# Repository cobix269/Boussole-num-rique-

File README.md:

# NORHALO

NORHALO est un projet de boussole numérique réalisé à l’aide d’un PCB qui permet à son utilisateur de retrouver le nord magnétique même dans le noir. Un écran lumineux affiche une flèche qui indique le nord grâce à un magnétomètre, des LEDs s’allument en fonction de la direction dans laquelle pointe la flèche.

**Figure 1 & 2 : visualisation 3D du PCB **  :    

## À propos :

Le projet est réalisé sous KiCad et comprend actuellement la conception du schéma électronique ainsi que celle du circuit imprimé et le code a implémenté dans le microcontrôleur.

## Composantes principales

| Type de composant | Référence / Modèle |
| :--- | :--- |
| **Accéléromètre** | MPU-6050 |
| **Alimentation** | USB-C |
| **Ecran** | *Non spécifié* |
| **LEDs** | WS2812B |
| **Level shifter** | 74AHCT1G125 |
| **Magnétomètre** | MMC5883MA |
| **Microcontrôleur** | STM32G071KBTxN |
| **Régulateur 3,3V** | AP2112K-3.3 |

---

**Fonctionnement** :

Le MMC5883MA est utilisé comme capteur magnétique pour mesurer le champ magnétique terrestre.

Le MPU-6050 apporte les informations inertielles permettant de prendre en compte l'orientation et les mouvements de la carte par rapport au sol.

Les données des capteurs sont traitées par le STM32G071KBTxN, qui peut déterminer la représentation de la direction à afficher.

Le code permet de fusionner ces données pour calculer un cap précis (compensé en inclinaison), puis met à jour l'écran central et pilote les LEDs (WS2812B) afin d'indiquer l'orientation.

## Alimentation :

La carte est prévue pour être alimentée via USB-C.

L'alimentation est ensuite régulée par un AP2112K-3.3 afin de fournir le domaine d'alimentation aux circuits fonctionnant en 3,3 V comme le microcontrôleur.

Le 74AHCT1G125 est utilisé dans la chaîne de commande des LED afin d'assurer l'interface logique entre le microcontrôleur et les WS2812B.

Les résistances sont utilisées comme résistance de pull-up pour le bus I2C, pour la configuration USB-C et pour la chaîne de commande des LEDs

Les condensateurs sont utilisés pour assurer le découplage local des circuits intégrés, la stabilisation de l’alimentation et le filtrage des variations rapides de tension.

Pour le placement des composants il est important que les condensateurs de découplage soient placés au plus près des composants qu’ils doivent découpler afin de réduire la longueur des connexions.

## Structure du projet

```text
.
└── Code_boussole 	       # code du projet               
    ├── Projet1.kicad_sch      # Schéma principal
    ├── Projet1.kicad_pcb      # Circuit imprimé
    ├── LED20.kicad_sch        # Schéma de l'affichage LED
    └── README.md              # Documentation du projet
```
Améliorations futures :

Passer sur batterie (LiPo / Li-Ion) : Ajoute un régulateur de charge USB et un circuit de basculement automatique entre l'USB et la batterie

Mesure de tension batterie : Ajoute un pont diviseur de tension connecté à une entrée ADC du STM32 pour afficher le pourcentage de batterie restant sur l'écran rond

Fusible réarmable : Ajoute une protection contre les surintensités juste après VBUS.

Visualisation du projet généré par IA :

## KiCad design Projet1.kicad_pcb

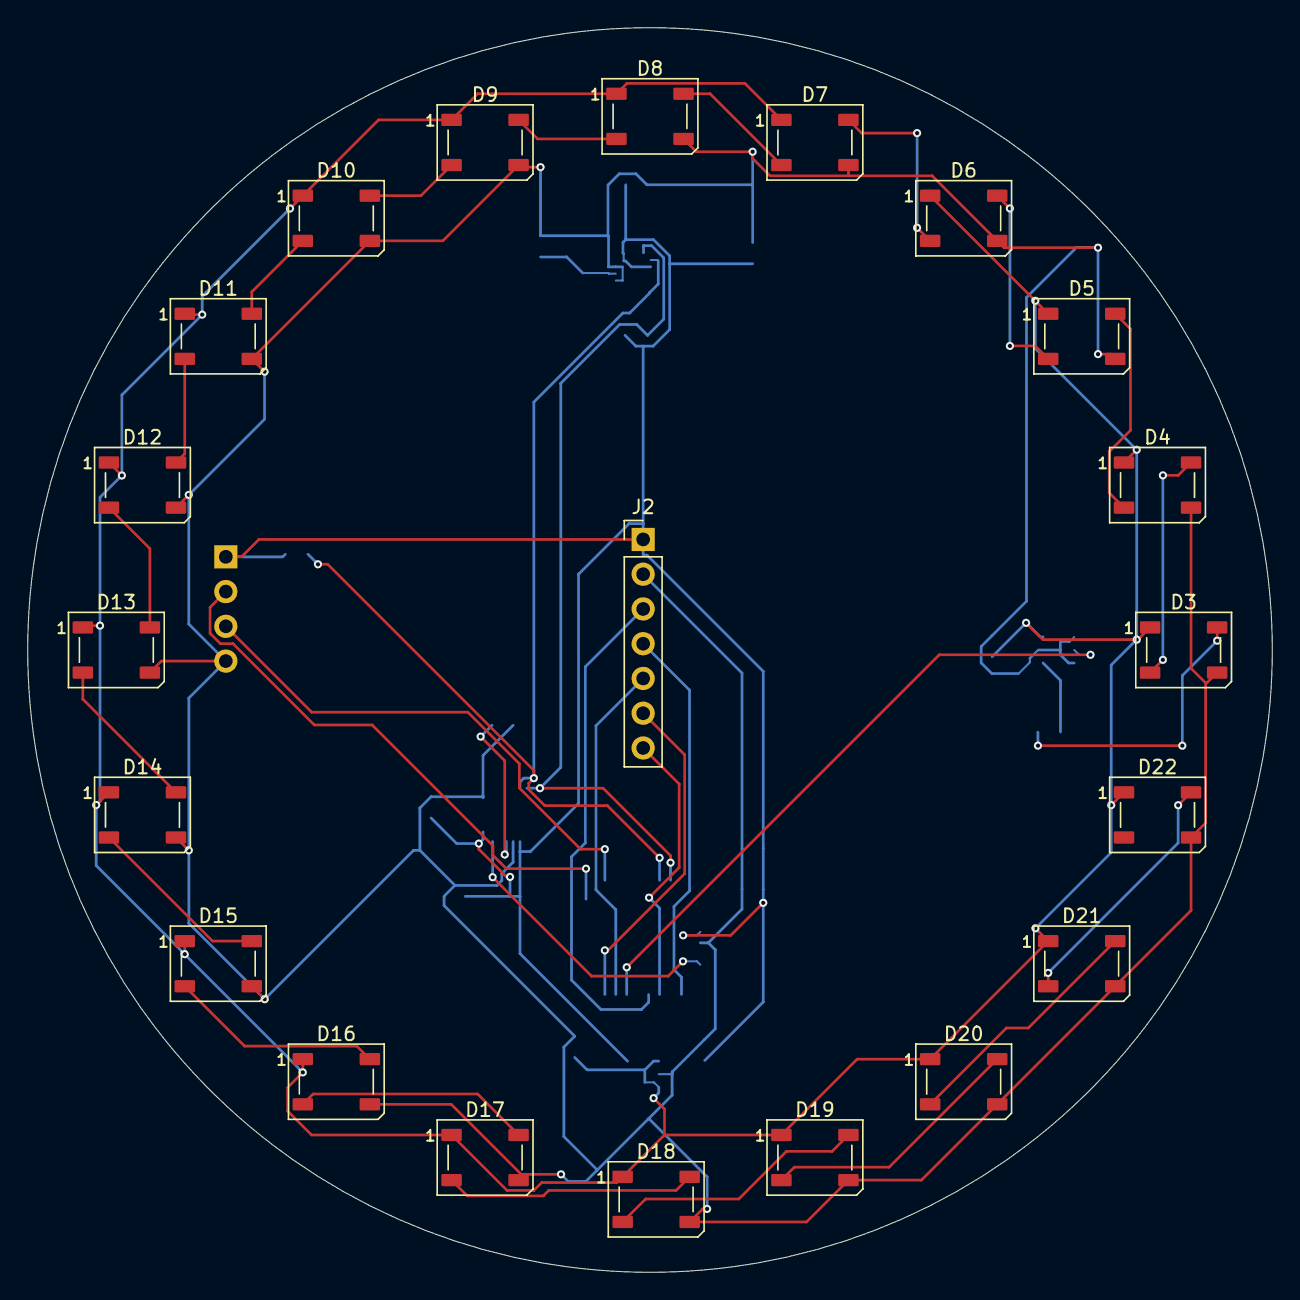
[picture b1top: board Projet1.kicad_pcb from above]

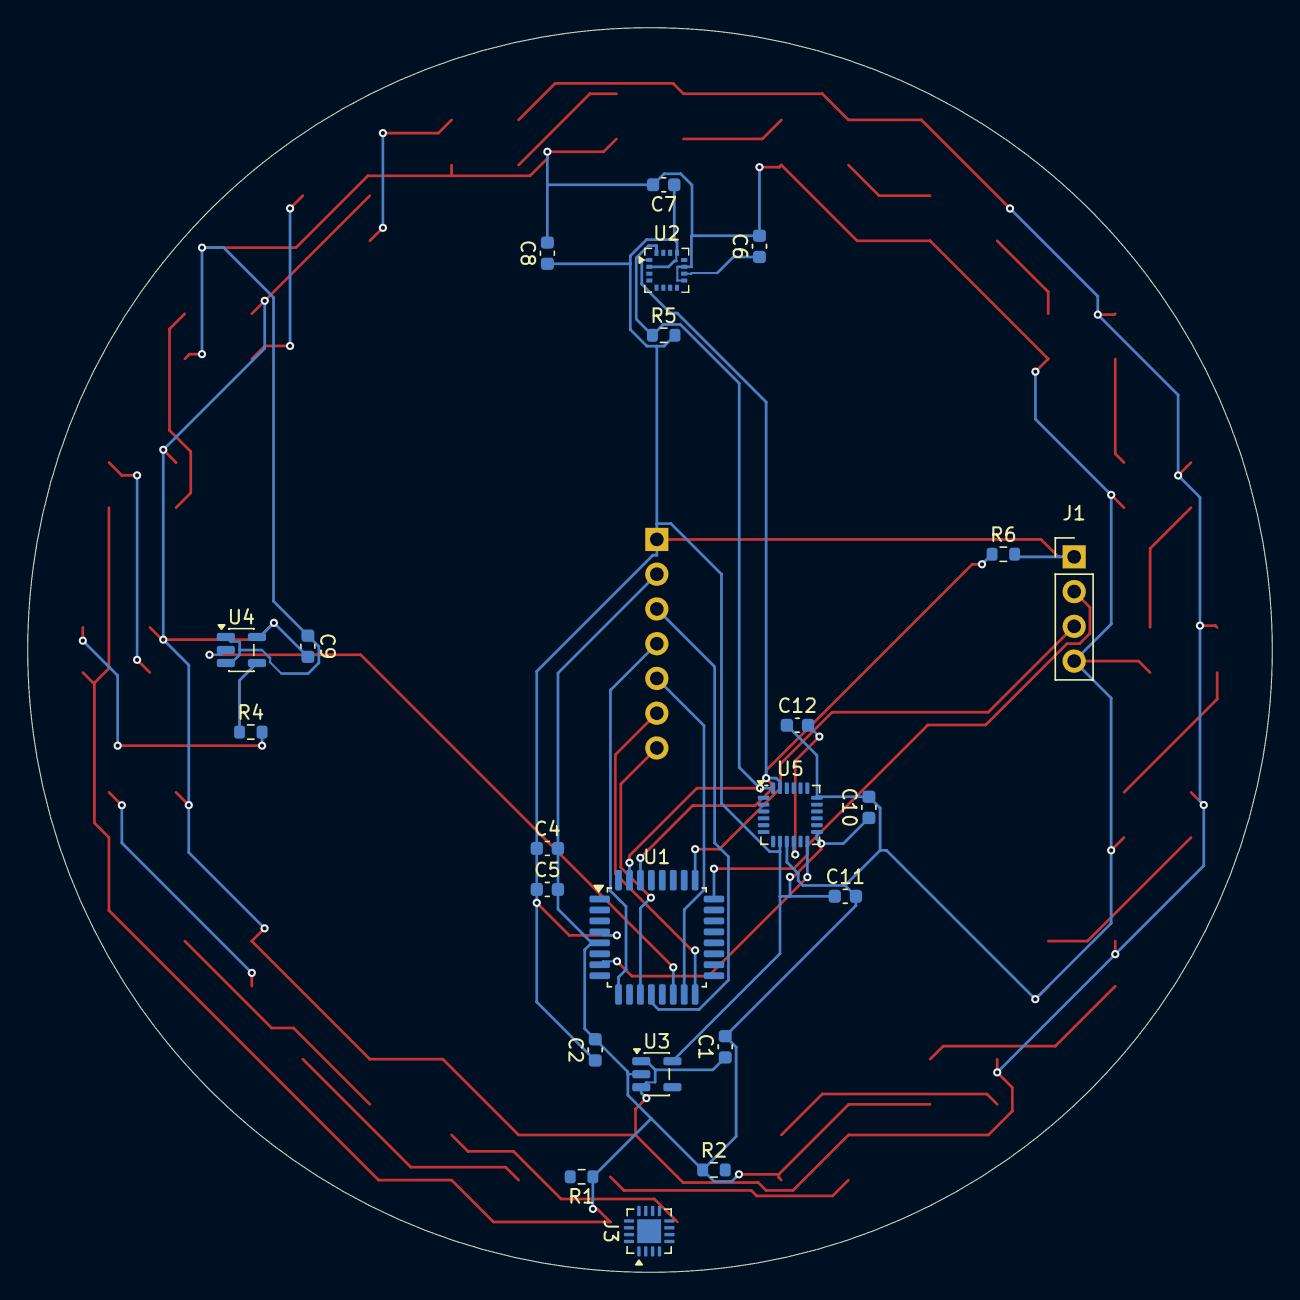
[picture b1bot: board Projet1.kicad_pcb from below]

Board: 2 copper layers, 91.0 x 91.0 mm, 44 parts (23 on the bottom side), 37 nets.

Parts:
C1, C2, C7: 1 µF; C_0603_1608Metric
C4, C8, C10: 100 nF; C_0603_1608Metric
C5: 4.7 µF; C_0603_1608Metric
C6: 10 µF; C_0603_1608Metric
C9: 100nF; C_0603_1608Metric
C11: 10; C_0603_1608Metric
C12: 10 nF; C_0603_1608Metric
D3, D4, D5, D6, D7, D8, D9, D10, D11, D12, D13, D14, D15, D16, D17, D18, D19, D20, D21, D22: WS2812B; LED_WS2812B_PLCC4_5.0x5.0mm_P3.2mm
J1: Conn_01x04; PinHeader_1x04_P2.54mm_Vertical
J2: Conn_01x07; PinHeader_1x07_P2.54mm_Vertical
J3: USB_C_Receptacle_PowerOnly_6P; WQFN-16-1EP_3x3mm_P0.5mm_EP1.75x1.75mm
R1, R2: 5.1 k; R_0603_1608Metric
R4: 330; R_0603_1608Metric
R5, R6: 2.7k; R_0603_1608Metric
U1: STM32G071KBTxN; LQFP-32_7x7mm_P0.8mm
U2: MMC5883MA; LGA-16_3x3mm_P0.5mm
U3: AP2112K-3.3; SOT-23-5
U4: 74AHCT1G125; SOT-23-5
U5: MPU-6050; InvenSense_QFN-24_4x4mm_P0.5mm

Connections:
+3.3V: C2.1, C4.1, C5.1, C7.1, C8.1, C10.1, C11.1, J1.1, J2.1, R5.2, R6.2, U1.4 (VDD), U2.2 (VDD), U2.13 (VDDIO), U3.5 (VOUT), U5.8 (VLOGIC), U5.13 (VDD)
+5V: C1.1, C9.2, D3.1 (VDD), D4.1 (VDD), D5.1 (VDD), D6.1 (VDD), D7.1 (VDD), D8.1 (VDD), D9.1 (VDD), D10.1 (VDD), D11.1 (VDD), D12.1 (VDD), D13.1 (VDD), D14.1 (VDD), D15.1 (VDD), D16.1 (VDD), D17.1 (VDD), D18.1 (VDD), D19.1 (VDD), D20.1 (VDD), D21.1 (VDD), D22.1 (VDD), U3.1 (VIN), U3.3 (EN), U4.5 (VCC)
/20 LEDS/LED_DATA_5V: R4.1, U4.4
ACC: U1.7 (PA0), U5.12 (INT)
GND: C1.2, C2.2, C4.2, C5.2, C6.2, C7.2, C8.2, C9.1, C10.2, C11.2, C12.1, D3.3 (VSS), D4.3 (VSS), D5.3 (VSS), D6.3 (VSS), D7.3 (VSS), D8.3 (VSS), D9.3 (VSS), D10.3 (VSS), D11.3 (VSS), D12.3 (VSS), D13.3 (VSS), D14.3 (VSS), D15.3 (VSS), D16.3 (VSS), D17.3 (VSS), D18.3 (VSS), D19.3 (VSS), D20.3 (VSS), D21.3 (VSS), D22.3 (VSS), J1.4, J2.2, R1.1, R2.1, U1.5 (VSS), U2.9 (GND), U2.11 (GND), U3.2 (GND), U4.1, U4.3 (GND), U5.9 (AD0), U5.18 (GND)
I2C_SCL: R6.1, U1.30 (PB6), U2.1 (SCL), U5.23 (SCL)
I2C_SDA: R5.1, U1.31 (PB7), U2.16 (SDA), U5.24 (SDA)
LCD_CS: J2.7, U1.11 (PA4)
LCD_DC: J2.5, U1.15 (PB0)
LCD_MOSI: J2.4, U1.9 (PA2)
LCD_RST: J2.6, U1.16 (PB1)
LCD_SCK: J2.3, U1.12 (PA5)
LED_DATA: U1.14 (PA7), U4.2
unnamed: D3.4 (DIN), R4.2
unnamed: D3.2 (DOUT), D4.4 (DIN)
unnamed: D4.2 (DOUT), D5.4 (DIN)
unnamed: D5.2 (DOUT), D6.4 (DIN)
unnamed: D6.2 (DOUT), D7.4 (DIN)
unnamed: D7.2 (DOUT), D8.4 (DIN)
unnamed: D8.2 (DOUT), D9.4 (DIN)
unnamed: D9.2 (DOUT), D10.4 (DIN)
unnamed: D10.2 (DOUT), D11.4 (DIN)
unnamed: D11.2 (DOUT), D12.4 (DIN)
unnamed: D12.2 (DOUT), D13.4 (DIN)
unnamed: D13.2 (DOUT), D14.4 (DIN)
unnamed: D14.2 (DOUT), D15.4 (DIN)
unnamed: D15.2 (DOUT), D16.4 (DIN)
unnamed: D16.2 (DOUT), D17.4 (DIN)
unnamed: D17.2 (DOUT), D18.4 (DIN)
unnamed: D18.2 (DOUT), D19.4 (DIN)
unnamed: D19.2 (DOUT), D20.4 (DIN)
unnamed: D20.2 (DOUT), D21.4 (DIN)
unnamed: D21.2 (DOUT), D22.4 (DIN)
unnamed: C6.1, U2.10 (CAP)
unnamed: C12.2, U5.10 (REGOUT)
SWD_CLK: J1.3, U1.25 (PA14)
SWD_I0: J1.2, U1.24 (PA13)
